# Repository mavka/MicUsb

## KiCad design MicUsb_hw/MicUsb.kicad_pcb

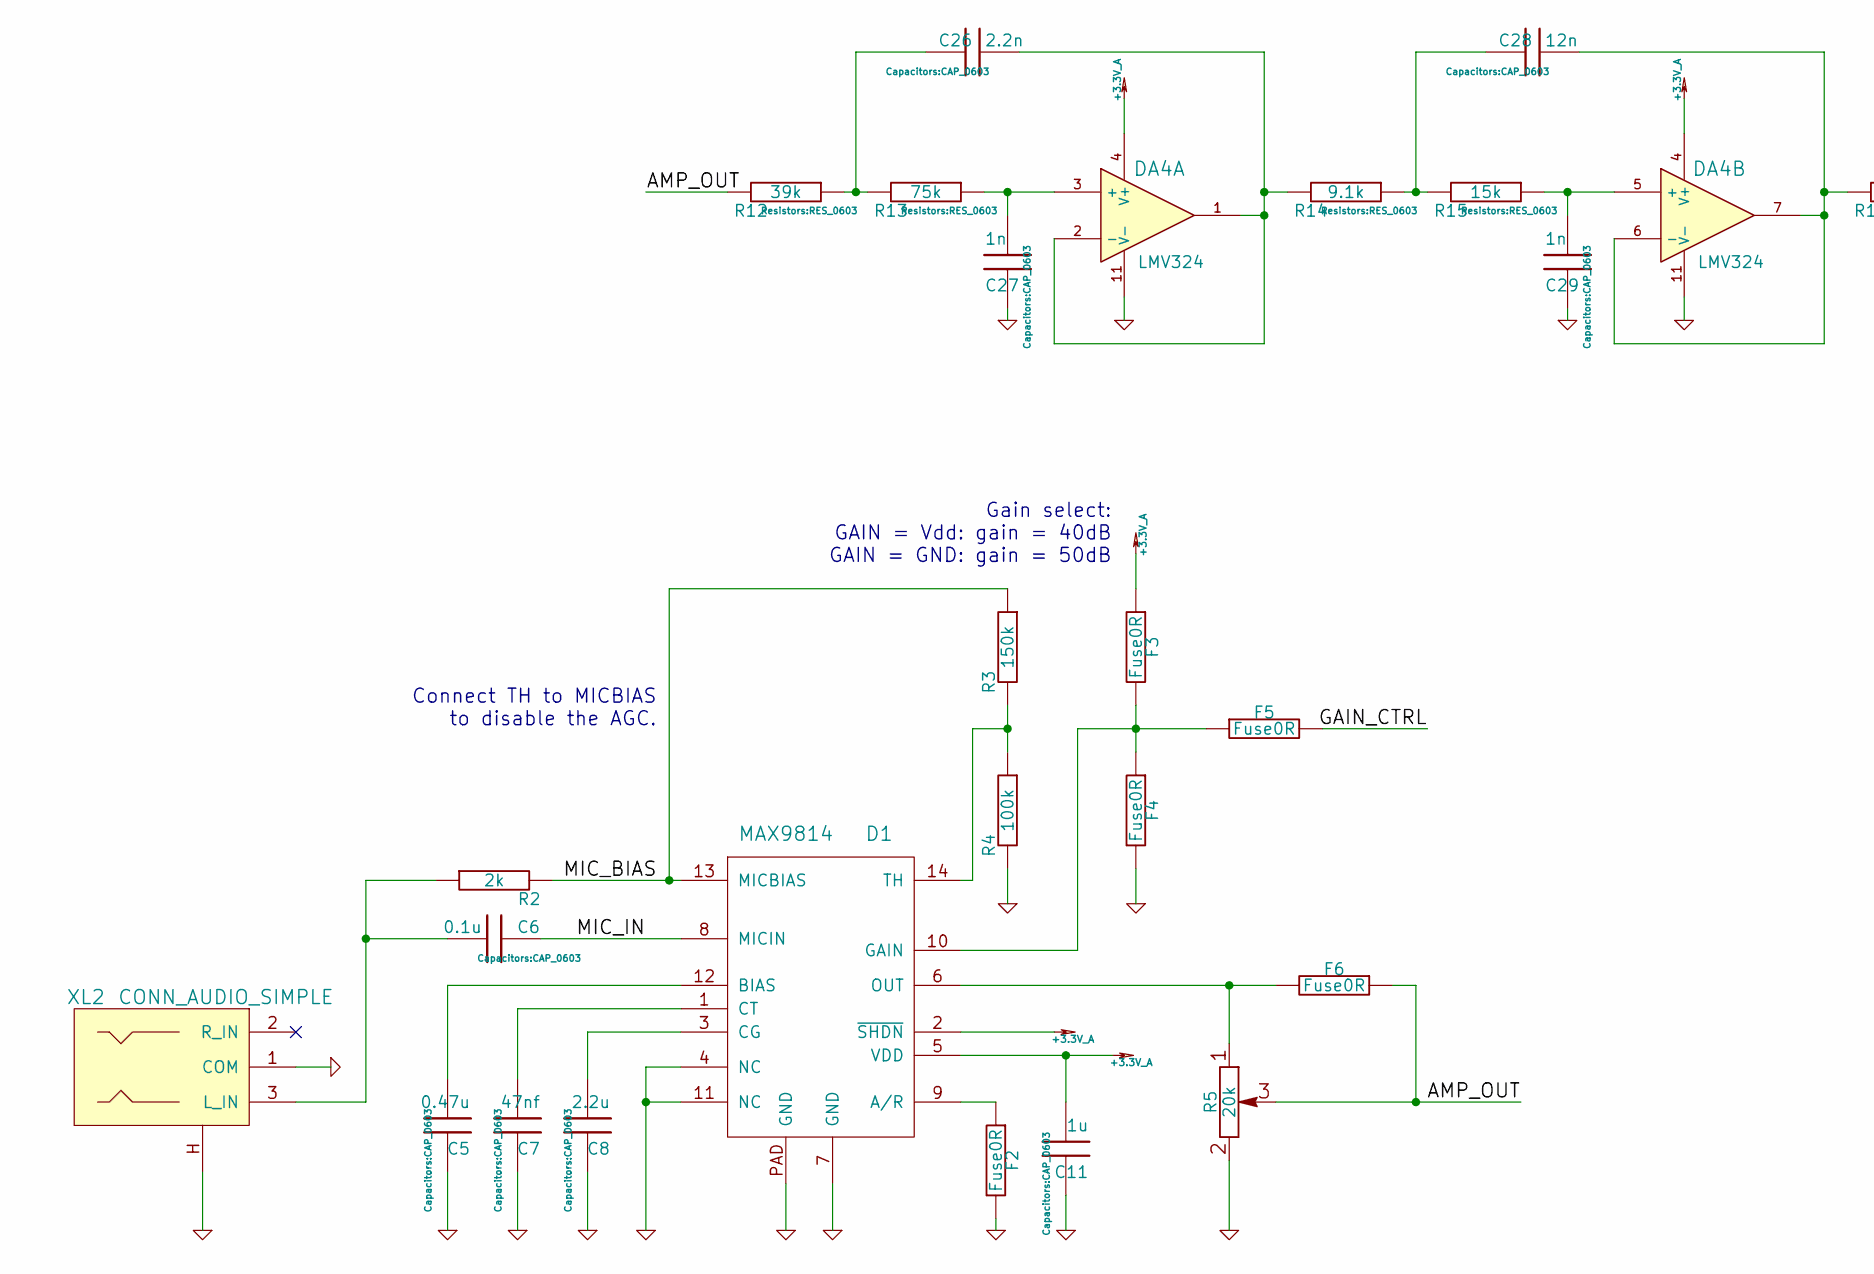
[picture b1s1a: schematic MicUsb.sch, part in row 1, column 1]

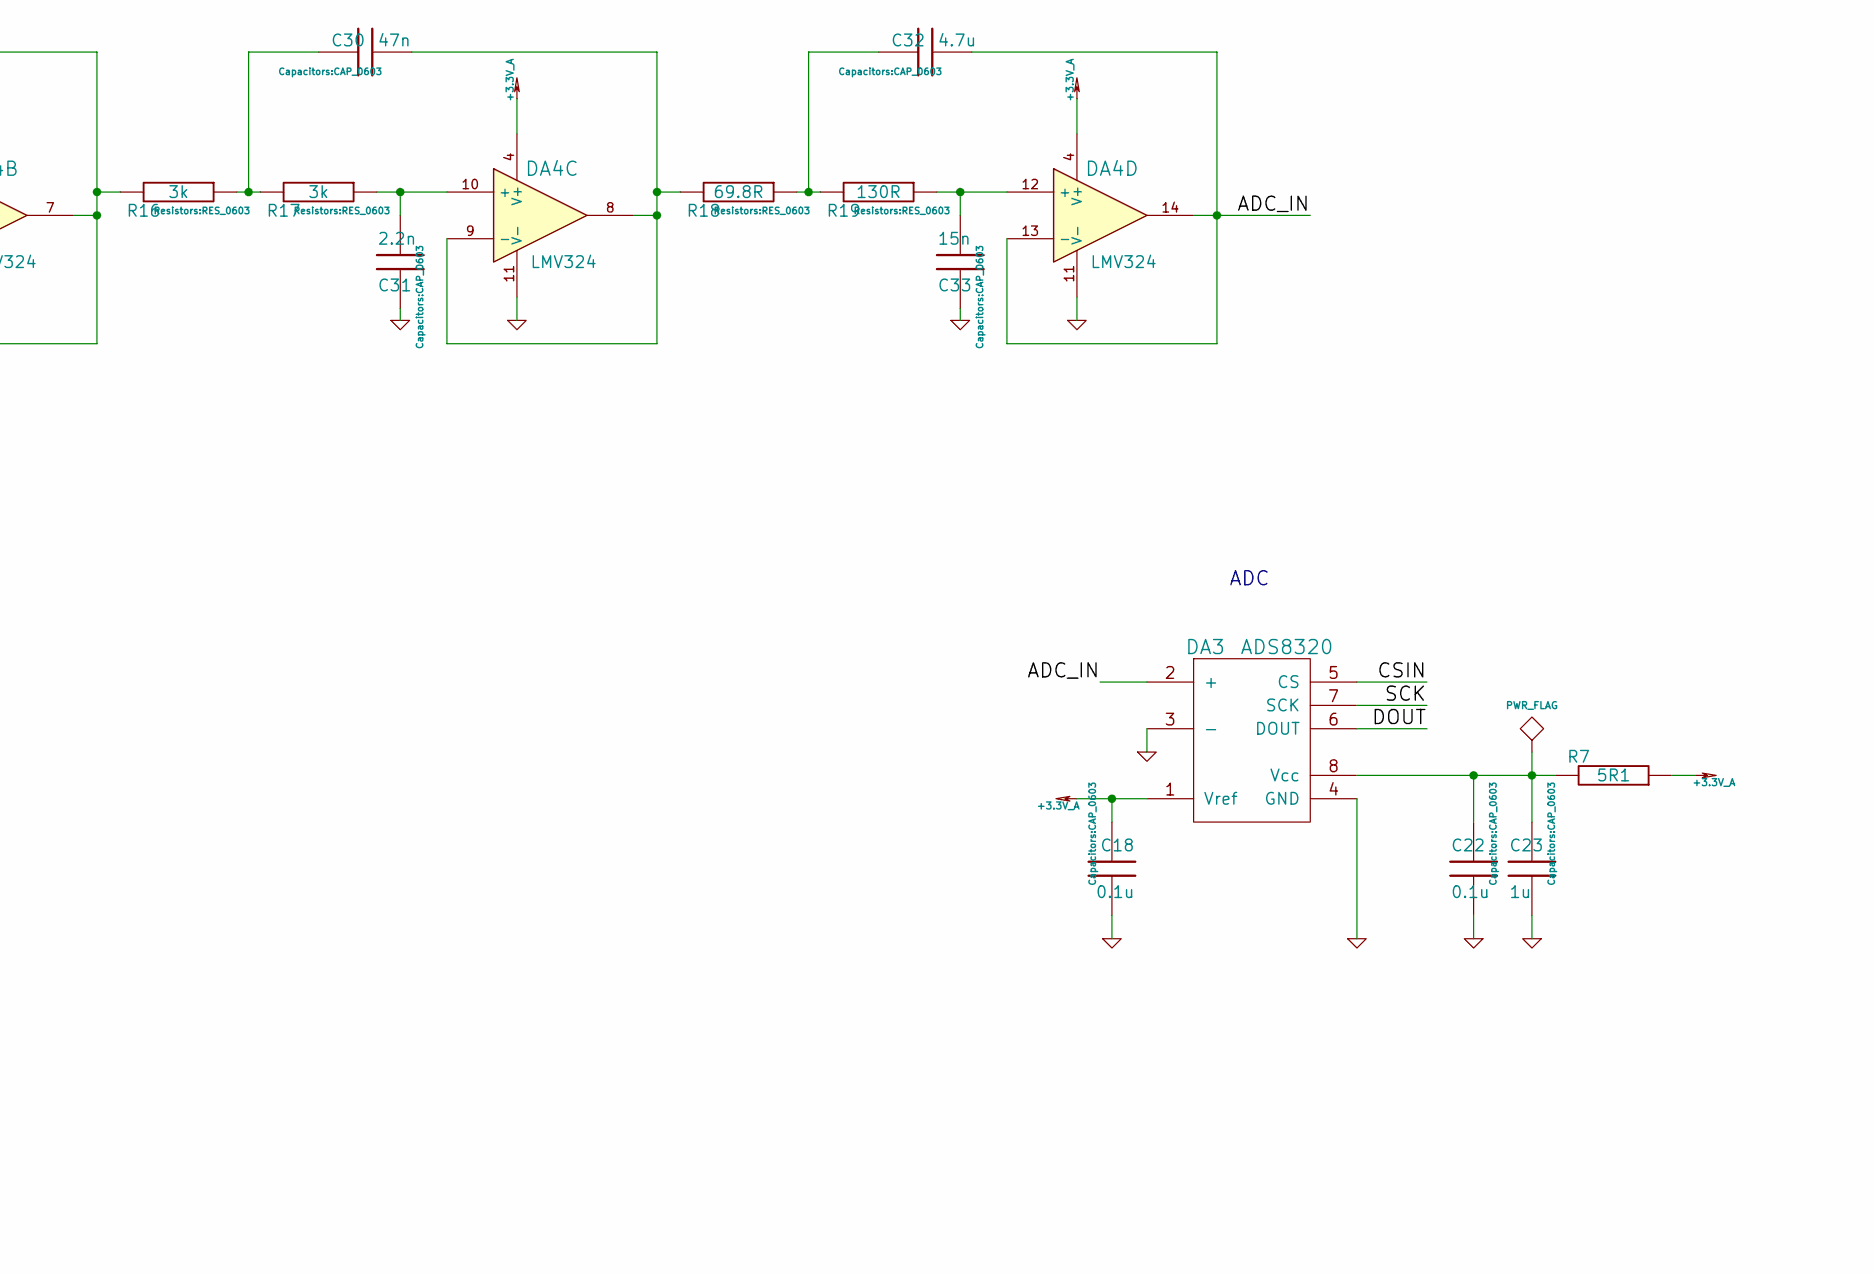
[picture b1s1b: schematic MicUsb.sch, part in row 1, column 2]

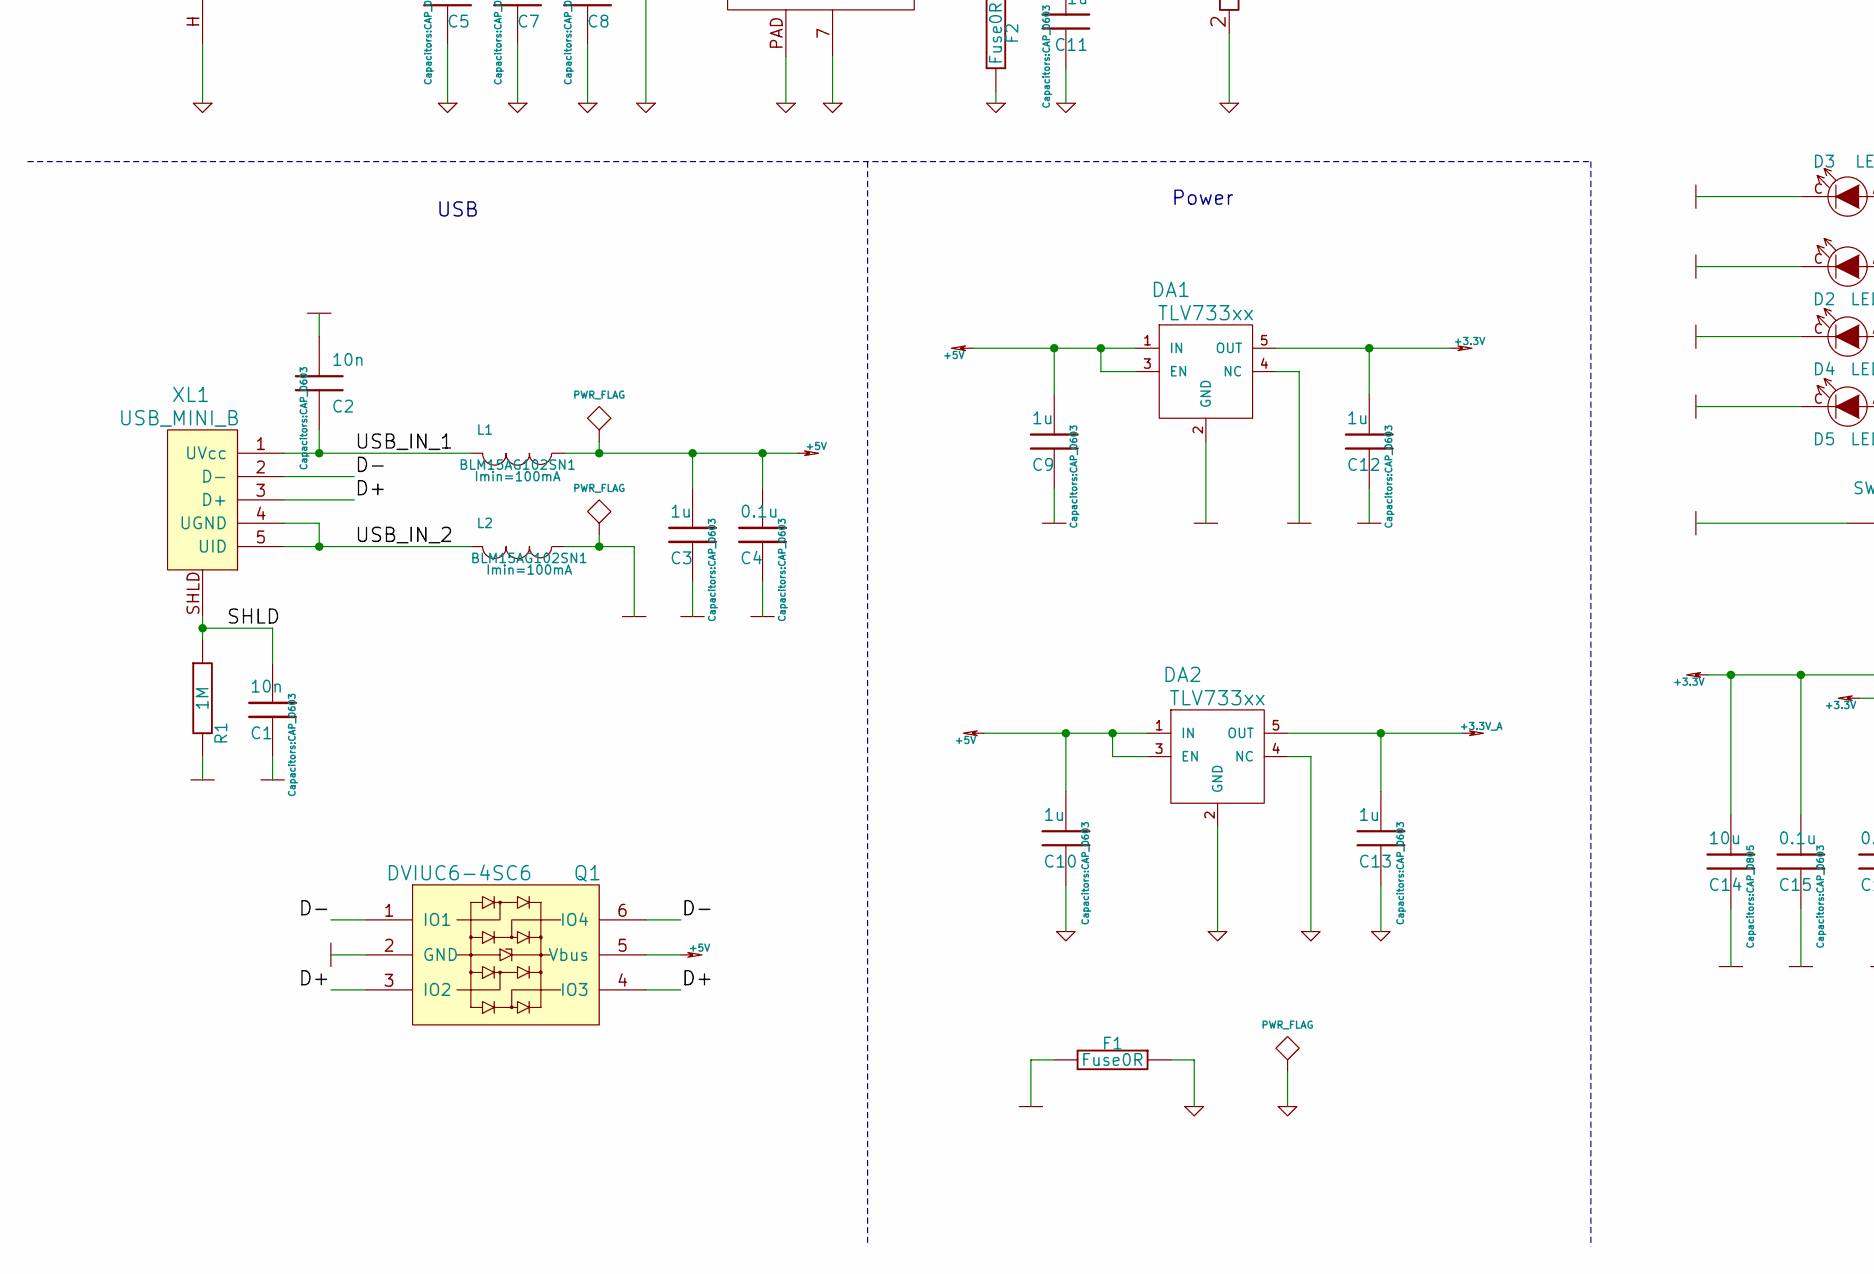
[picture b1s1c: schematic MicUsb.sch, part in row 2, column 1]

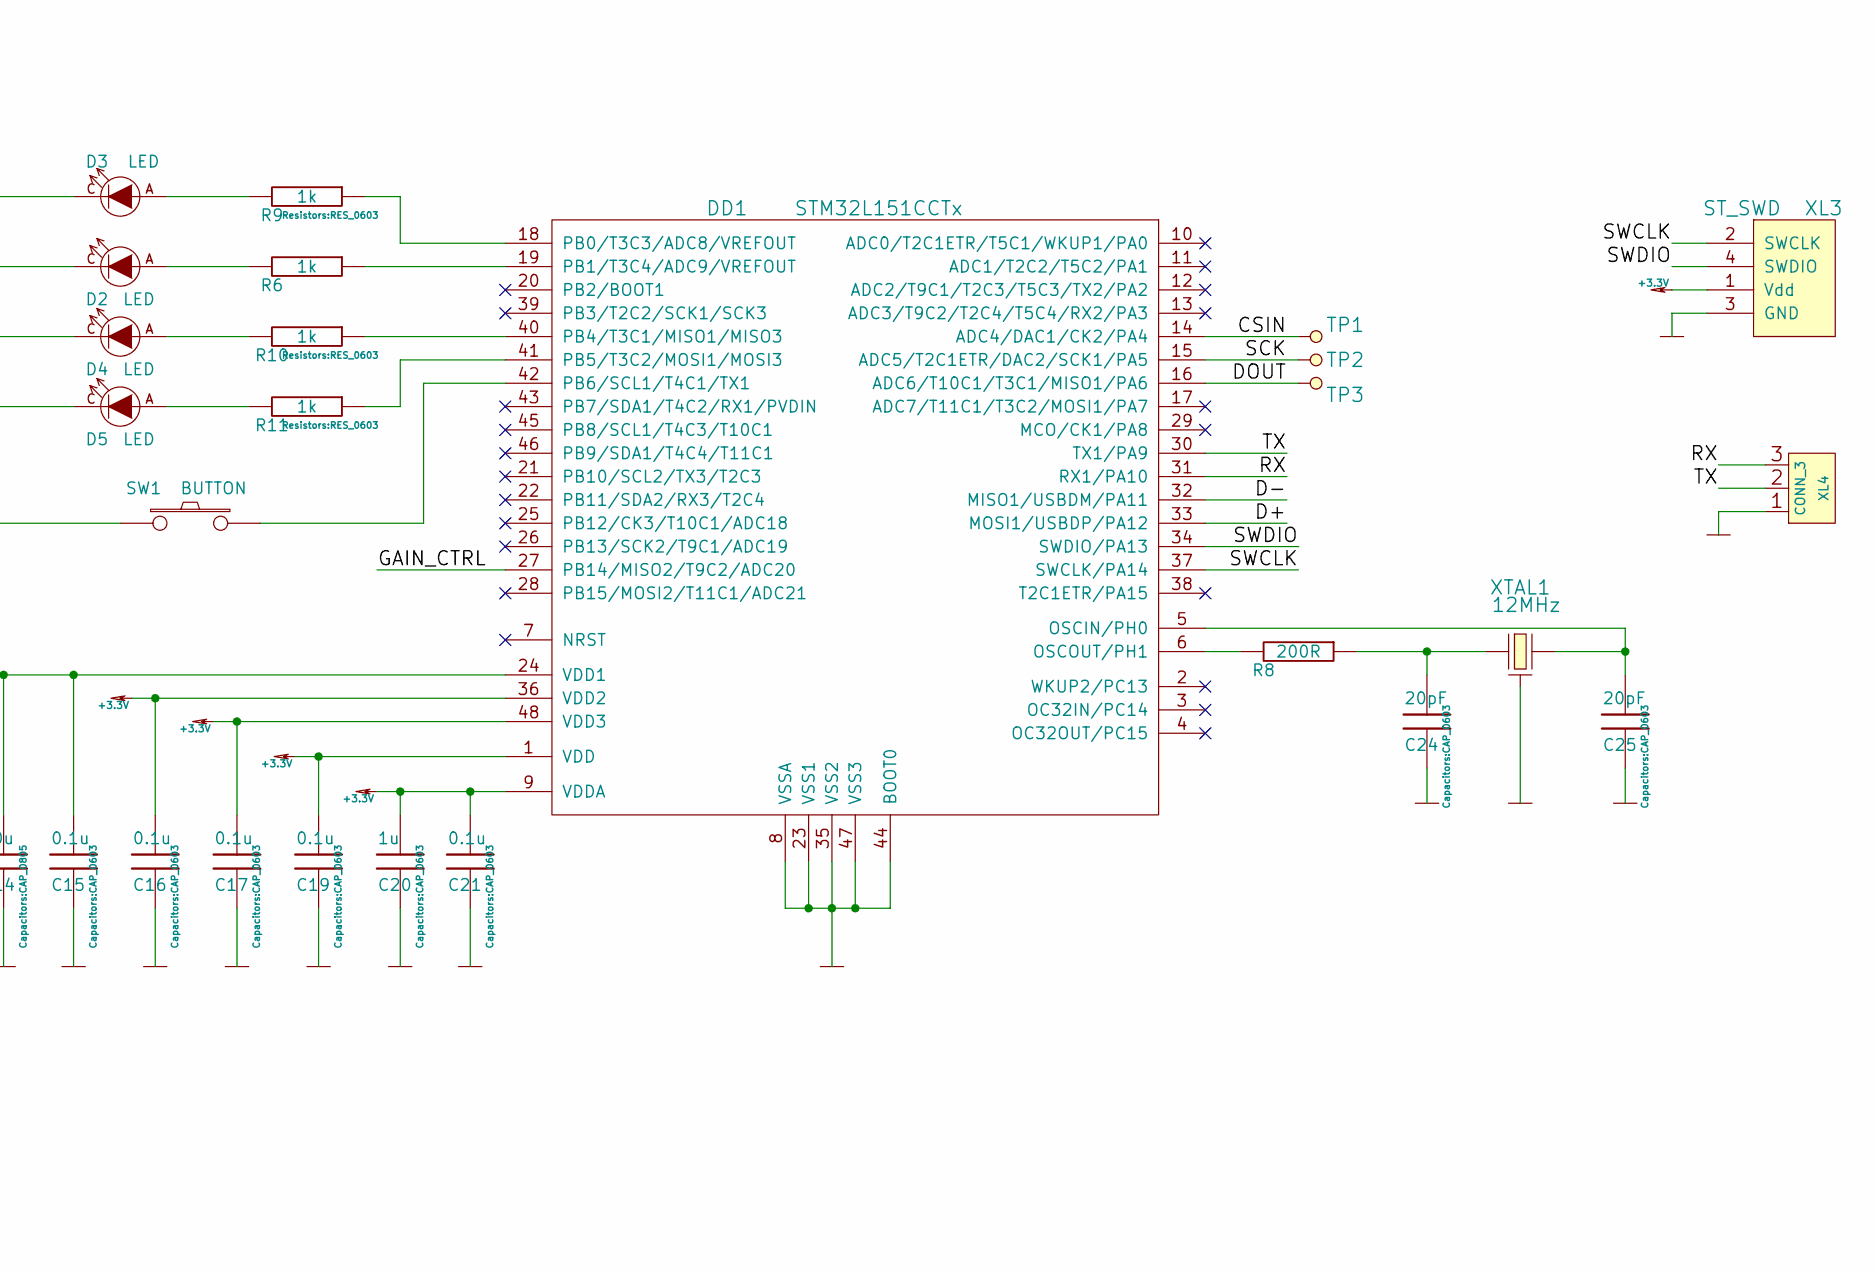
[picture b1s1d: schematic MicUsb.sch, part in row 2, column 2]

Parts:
C1, C2: 10n; CAP_0603
C3, C9, C10, C11, C12, C13, C20, C23: 1u; CAP_0603
C4, C6, C15, C16, C17, C18, C19, C21, C22: 0.1u; CAP_0603
C5: 0.47u; CAP_0603
C7: 47nf; CAP_0603
C8: 2.2u; CAP_0603
C14: 10u; CAP_0805
C24, C25: 20pF; CAP_0603
C26, C31: 2.2n; CAP_0603
C27, C29: 1n; CAP_0603
C28: 12n; CAP_0603
C30: 47n; CAP_0603
C32: 4.7u; CAP_0603
C33: 15n; CAP_0603
D1: MAX9814; DFN14
D2, D3, D4, D5: LED; LED_Through-Hole-3mm
DA1, DA2: TLV733xx; SOT23-5
DA3: ADS8320; MSOP8
DA4: LMV324; SO14
DD1: STM32L151CCTx; LQFP48
F1, F2, F3, F4, F5, F6: Fuse0R; RES_0603_SOLDERFUSE
L1, L2: BLM15AG102SN1; IND_0402
Q1: DVIUC6-4SC6; SOT23-6
R1: 1M; RES_0603
R2: 2k; RES_0603
R3: 150k; RES_0603
R4: 100k; RES_0603
R5: 20k; VAR_PTV09A-4
R6, R9, R10, R11: 1k; RES_0603
R7: 5R1; RES_0603
R8: 200R; RES_0603
R12: 39k; RES_0603
R13: 75k; RES_0603
R14: 9.1k; RES_0603
R15: 15k; RES_0603
R16, R17: 3k; RES_0603
R18: 69.8R; RES_0603
R19: 130R; RES_0603
SW1: BUTTON; BTN_6x6
TP1, TP2, TP3: TESTPOINT; TESTPOINT_1MM
XL1: USB_MINI_B; USBmicro_MOLEX_WM17142
XL2: CONN_AUDIO_SIMPLE; AUDIO_CKX3_5_30
XL3: ST_SWD; PLS-4
XL4: CONN_3; PLS-3
XTAL1: 12MHz; 0503x4-4

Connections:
+3.3V: C12.1, C14.1, C15.1, C16.1, C17.1, C19.1, C20.1, C21.1, DA1.5 (OUT), DD1.1 (VDD), DD1.9 (VDDA), DD1.24 (VDD1), DD1.36 (VDD2), DD1.48 (VDD3), XL3.1 (Vdd)
+3.3V_A: C11.1, C13.1, C18.2, D1.2 (~SHDN), D1.5 (VDD), DA2.5 (OUT), DA3.1 (Vref), DA4.4 (V+), F3.1, R7.1
+5V: C3.1, C4.1, C9.1, C10.1, DA1.1 (IN), DA1.3 (EN), DA2.1 (IN), DA2.3 (EN), L1.1, Q1.5 (Vbus)
/ADC_IN: C32.1, DA3.2 (+), DA4.13 (-), DA4.14
/AMP_OUT: F6.1, R5.3, R12.2
/CSIN: DA3.5 (CS), DD1.14 (ADC4/DAC1/CK2/PA4), TP1.1
/D+: DD1.33 (MOSI1/USBDP/PA12), Q1.3 (IO2), Q1.4 (IO3), XL1.3 (D+)
/D-: DD1.32 (MISO1/USBDM/PA11), Q1.1 (IO1), Q1.6 (IO4), XL1.2 (D-)
/DOUT: DA3.6 (DOUT), DD1.16 (ADC6/T10C1/T3C1/MISO1/PA6), TP3.1
/GAIN_CTRL: DD1.27 (PB14/MISO2/T9C2/ADC20), F5.2
/MIC_BIAS: D1.13 (MICBIAS), R2.2, R3.1
/MIC_IN: C6.2, D1.8 (MICIN)
/RX: DD1.31 (RX1/PA10), XL4.3
/SCK: DA3.7 (SCK), DD1.15 (ADC5/T2C1ETR/DAC2/SCK1/PA5), TP2.1
/SHLD: C1.1, R1.1, XL1.SHLD
/SWCLK: DD1.37 (SWCLK/PA14), XL3.2 (SWCLK)
/SWDIO: DD1.34 (SWDIO/PA13), XL3.4 (SWDIO)
/TX: DD1.30 (TX1/PA9), XL4.2 (PM)
/USB_IN_1: C2.2, L1.2, XL1.1 (UVcc)
/USB_IN_2: L2.2, XL1.4 (UGND), XL1.5 (UID)
AGND: C5.2, C7.2, C8.2, C10.2, C11.2, C13.2, C18.1, C22.1, C23.1, C27.2, C29.2, C31.2, C33.2, D1.4 (NC), D1.7 (GND), D1.11 (NC), D1.PAD (GND), DA2.2 (GND), DA2.4 (NC), DA3.3 (-), DA3.4 (GND), DA4.11 (V-), F1.1, F2.2, F4.2, R4.2, R5.2, XL2.1 (COM), XL2.H
GND: C1.2, C2.1, C3.2, C4.2, C9.2, C12.2, C14.2, C15.2, C16.2, C17.2, C19.2, C20.2, C21.2, C24.2, C25.2, D2.C, D3.C, D4.C, D5.C, DA1.2 (GND), DA1.4 (NC), DD1.8 (VSSA), DD1.23 (VSS1), DD1.35 (VSS2), DD1.44 (BOOT0), DD1.47 (VSS3), F1.2, L2.1, Q1.2 (GND), R1.2, SW1.1, XL3.3 (GND), XL4.1, XTAL1.H
unnamed: C5.1, D1.12 (BIAS)
unnamed: C6.1, R2.1, XL2.3 (L_IN)
unnamed: C7.1, D1.1 (CT)
unnamed: C8.1, D1.3 (CG)
unnamed: C22.2, C23.2, DA3.8 (Vcc), R7.2
unnamed: C24.1, R8.1, XTAL1.1
unnamed: C25.1, DD1.5 (OSCIN/PH0), XTAL1.2
unnamed: C26.1, DA4.1, DA4.2 (-), R14.2
unnamed: C26.2, R12.1, R13.2
unnamed: C27.1, DA4.3 (+), R13.1
unnamed: C28.1, DA4.6 (-), DA4.7, R16.2
unnamed: C28.2, R14.1, R15.2
unnamed: C29.1, DA4.5 (+), R15.1
unnamed: C30.1, DA4.8, DA4.9 (-), R18.2
unnamed: C30.2, R16.1, R17.2
unnamed: C31.1, DA4.10 (+), R17.1
unnamed: C32.2, R18.1, R19.2
unnamed: C33.1, DA4.12 (+), R19.1
unnamed: D1.6 (OUT), F6.2, R5.1
unnamed: D1.9 (A/R), F2.1
unnamed: D1.10 (GAIN), F3.2, F4.1, F5.1
unnamed: D1.14 (TH), R3.2, R4.1
unnamed: D2.A, R6.2
unnamed: D3.A, R9.2
unnamed: D4.A, R10.2
unnamed: D5.A, R11.2
unnamed: DD1.6 (OSCOUT/PH1), R8.2
unnamed: DD1.18 (PB0/T3C3/ADC8/VREFOUT), R9.1
unnamed: DD1.19 (PB1/T3C4/ADC9/VREFOUT), R6.1
unnamed: DD1.40 (PB4/T3C1/MISO1/MISO3), R10.1
unnamed: DD1.41 (PB5/T3C2/MOSI1/MOSI3), R11.1
unnamed: DD1.42 (PB6/SCL1/T4C1/TX1), SW1.2

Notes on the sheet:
Power
USB
Connect TH to MICBIAS to disable the AGC.
Gain select: GAIN = Vdd: gain = 40dB GAIN = GND: gain = 50dB
ADC

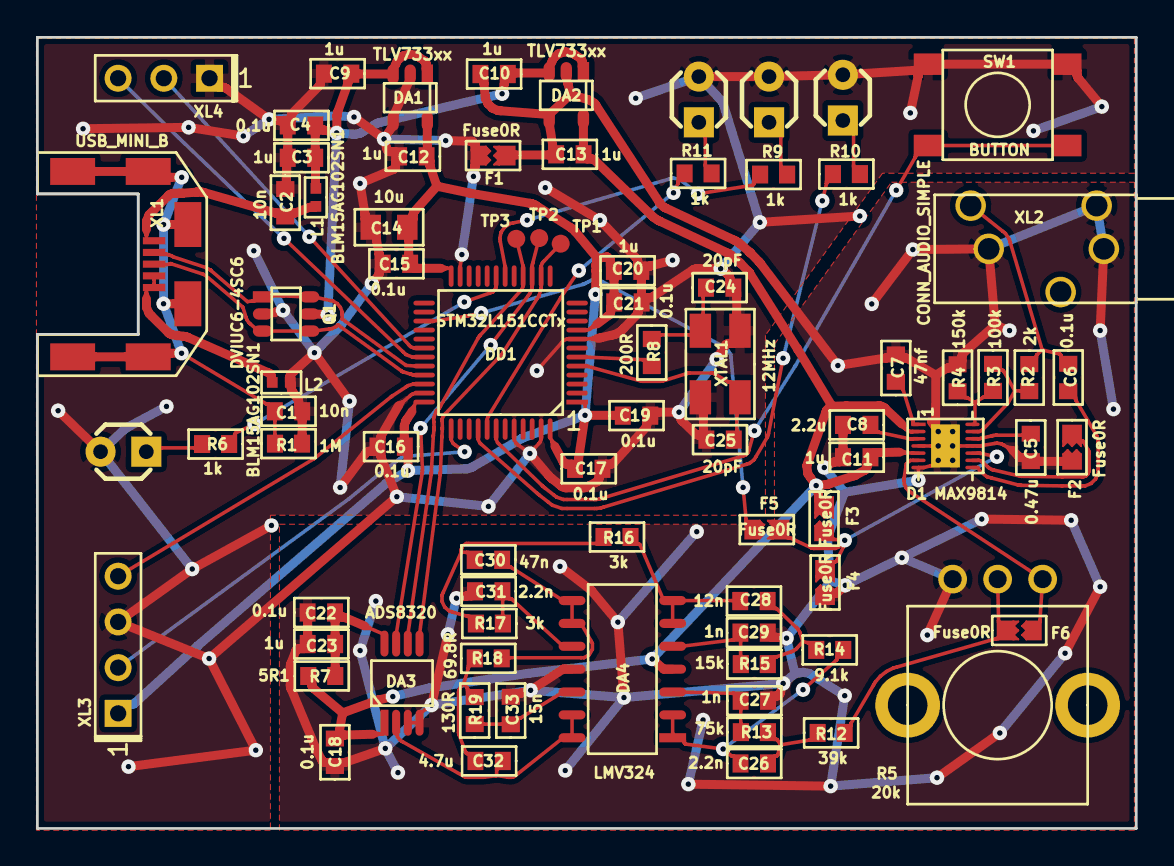
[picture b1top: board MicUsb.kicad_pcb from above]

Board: 2 copper layers, 61.0 x 44.0 mm, 80 parts (0 on the bottom side), 54 nets.

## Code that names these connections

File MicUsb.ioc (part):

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Mcu.Name=STM32L151CCUx
Mcu.Package=UFQFPN48
Mcu.UserName=STM32L151CCUx
PA10.Mode=Asynchronous
PA10.Signal=USART1_RX
PA11.Mode=Device
PA11.Signal=USB_DM
PA12.Mode=Device
PA12.Signal=USB_DP
PA13.Mode=Serial-Wire
PA13.Signal=SYS_JTMS-SWDIO
PA14.Mode=Serial-Wire
PA14.Signal=SYS_JTCK-SWCLK
PA4.Mode=NSS_Signal_Hard
PA4.Signal=SPI1_NSS
PA5.Mode=Full_Duplex_Master
PA5.Signal=SPI1_SCK
PA6.Mode=Full_Duplex_Master
PA6.Signal=SPI1_MISO
PA7.Mode=Full_Duplex_Master
PA7.Signal=SPI1_MOSI
PA9.Mode=Asynchronous
PA9.Signal=USART1_TX
PB0.GPIOParameters=GPIO_Label
PB0.GPIO_Label=LED2
PB0.Signal=S_TIM3_CH3
PB1.GPIOParameters=GPIO_Label
PB1.GPIO_Label=LED1
PB1.Signal=S_TIM3_CH4
PB4.GPIOParameters=GPIO_Label
PB4.GPIO_Label=LED4
PB4.Signal=S_TIM3_CH1
PB5.GPIOParameters=GPIO_Label
PB5.GPIO_Label=LED3
PB5.Signal=S_TIM3_CH2
PB6.GPIOParameters=GPIO_Label
PB6.GPIO_Label=BUTTON
PB6.Signal=S_TIM4_CH1
PH0-OSC_IN.Mode=HSE-External-Oscillator
PH0-OSC_IN.Signal=RCC_OSC_IN
PH1-OSC_OUT.Mode=HSE-External-Oscillator
PH1-OSC_OUT.Signal=RCC_OSC_OUT
RCC.HSE_VALUE=24000000
RCC.SYSCLKFreq_VALUE=2097000

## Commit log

2015-11-12 stm32 is so lonely
2015-11-17 + ioc, sch 20%
2015-11-18 sch update
2015-11-18 sch update, i need answers!
2015-11-20 * ADS
2015-11-20 * annotate, footprints
2015-11-20 small scheme updates
2015-11-22 + LP Filter simulations
2015-11-22 *cir
2015-11-23 + LP filter, i need answers!
2015-11-23 *filter
2015-11-23 * filter once more
2015-11-23 small scheme update
2015-11-24 just CvPcb
2015-11-24 + Firmware, not working
2015-11-26 * pcb 50%
2015-11-26 + plot
2015-11-26 plot again
2015-12-08 OS seems working
2015-12-08 32MHz CLK ok
2015-12-08 + USB
2015-12-10 * Disabled USB Hi Perf IRQ
2015-12-10 Back to Ostranna Studio
2015-12-10 + ADC seems working
2015-12-14 * Data sent using queue. Bad idea.
2015-12-14 - queue + Timer-controlled data sending Sound fading out time after time
2015-12-14 + Sync by SOF
2015-12-14 Clean-up
2015-12-15 add BOM link
2016-01-24 * ChSysHalt: + printf __FUNCTION__
2016-01-24 * Leds renamed + Kl_lib fast pin setup + Button regulated gain + Sch leds renamed
2016-01-24 * Buffer work made, no clicks
